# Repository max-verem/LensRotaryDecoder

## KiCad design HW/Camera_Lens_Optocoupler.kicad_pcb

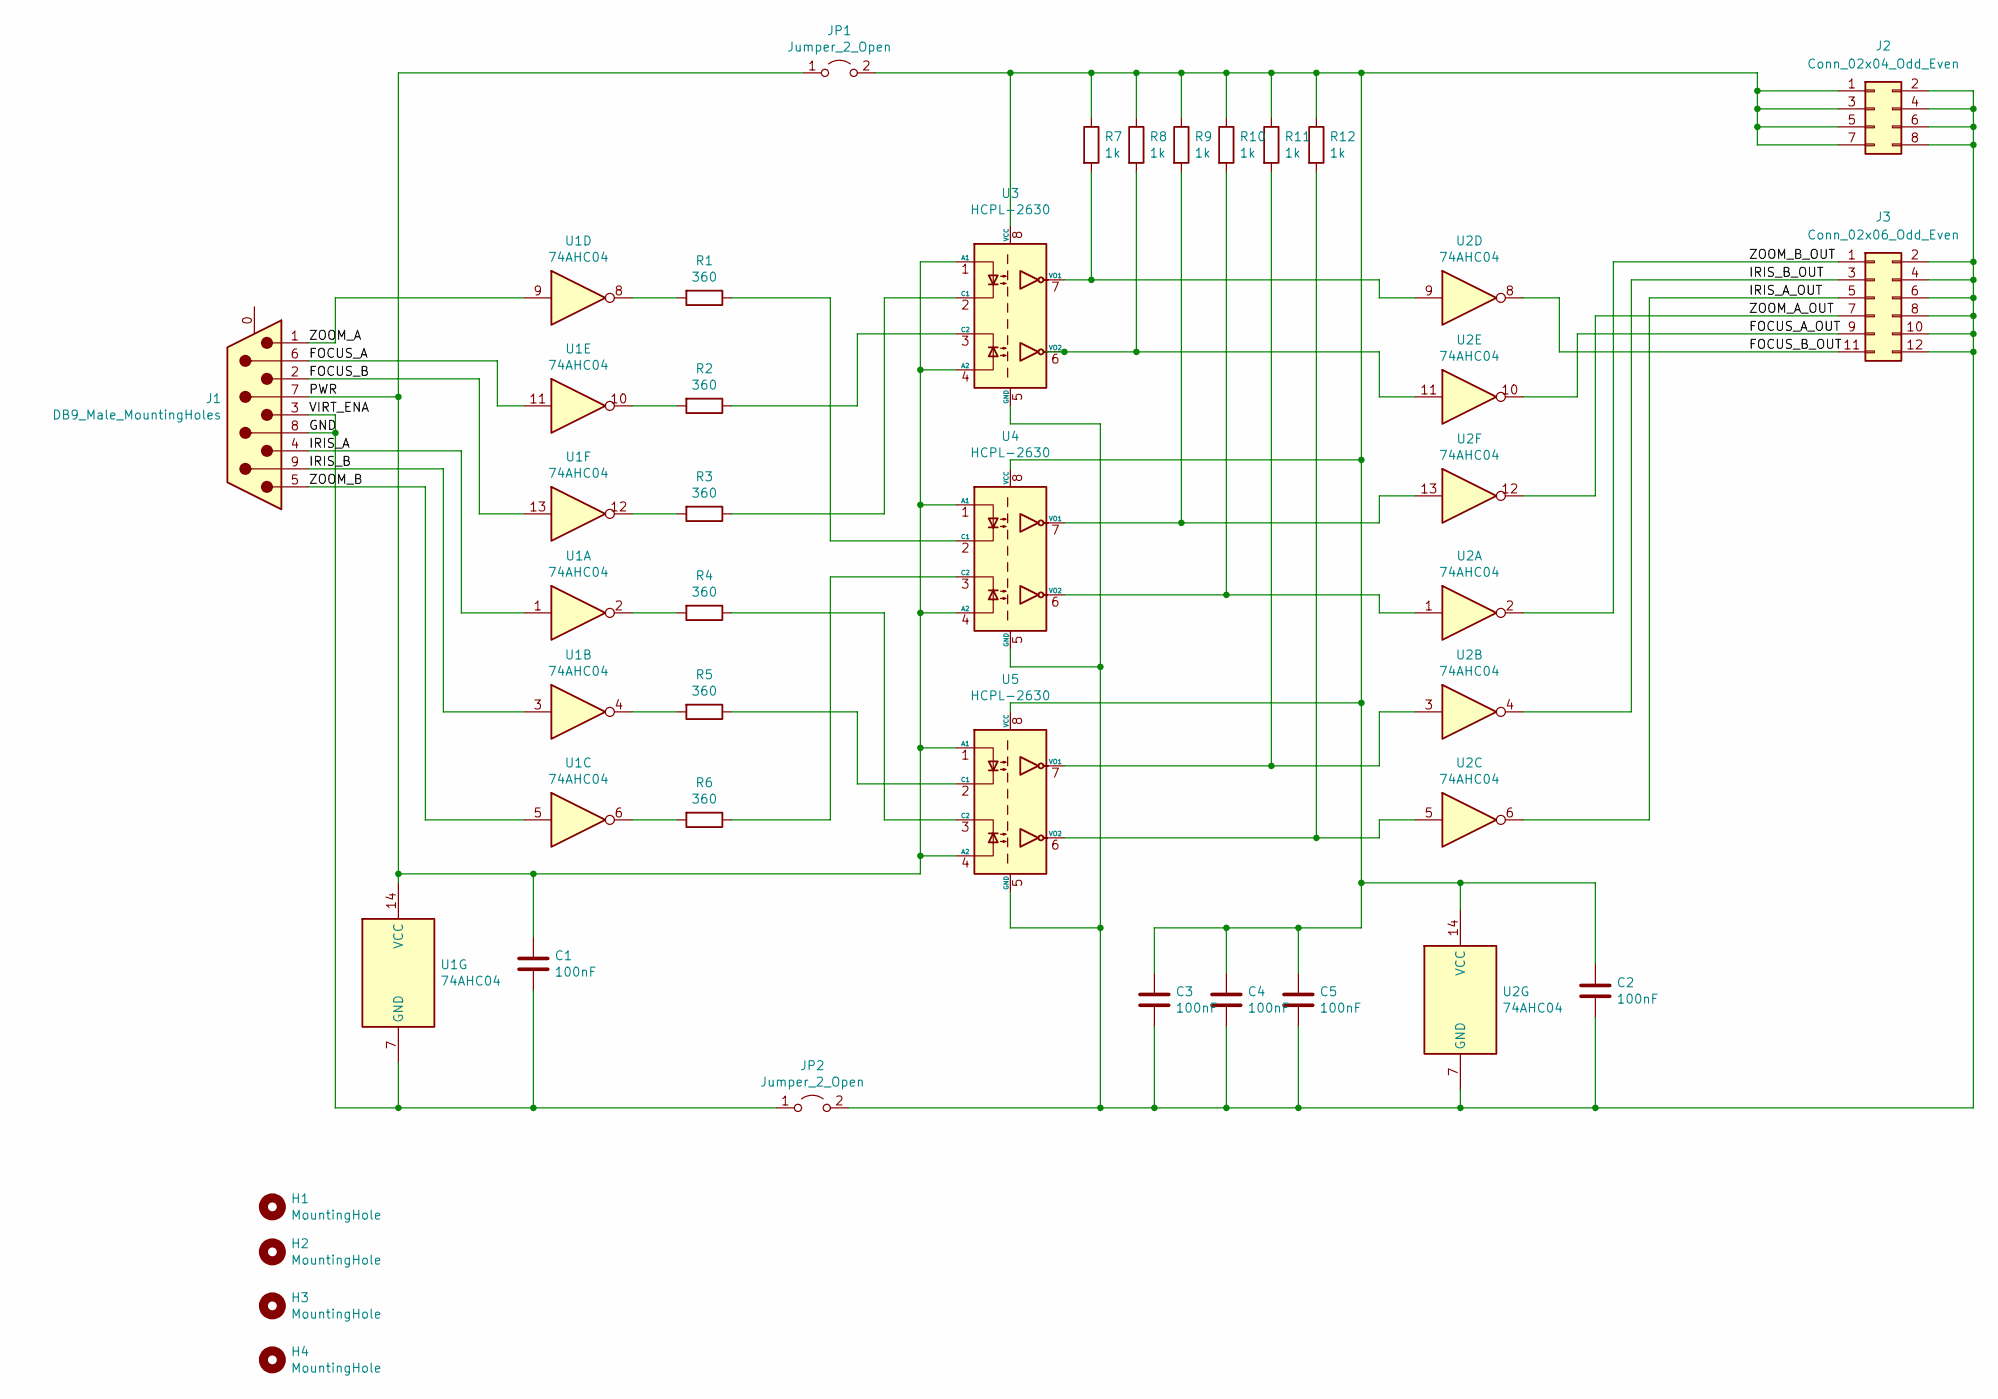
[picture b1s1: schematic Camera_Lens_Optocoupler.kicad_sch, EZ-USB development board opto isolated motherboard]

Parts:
C1, C2, C3, C4, C5: 100nF; C_Rect_L7.0mm_W2.0mm_P5.00mm
H1, H2, H3, H4: MountingHole; MountingHole_3.2mm_M3
J1: DB9_Male_MountingHoles; DSUB-9_Male_Horizontal_P2.77x2.84mm_EdgePinOffset9.90mm_Hou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
J2: Conn_02x04_Odd_Even; PinHeader_2x04_P2.54mm_Horizontal
J3: Conn_02x06_Odd_Even; PinSocket_2x06_P2.54mm_Horizontal
JP1, JP2: Jumper_2_Open; PinHeader_1x02_P2.54mm_Vertical
R1, R2, R3, R4, R5, R6: 360; R_Axial_DIN0309_L9.0mm_D3.2mm_P12.70mm_Horizontal
R7, R8, R9, R10, R11, R12: 1k; R_Axial_DIN0309_L9.0mm_D3.2mm_P12.70mm_Horizontal
U1, U2: 74AHC04; DIP-14_W7.62mm
U3, U4, U5: HCPL-2630; DIP-8_W7.62mm

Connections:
/FOCUS_A: J1.6, U1.11
/FOCUS_A_OUT: J3.9, U2.10
/FOCUS_B: J1.2, U1.13
/FOCUS_B_OUT: J3.11, U2.8
/GND: C1.2, J1.3, J1.8, JP2.1 (A), U1.7 (GND)
/IRIS_A: J1.4, U1.1
/IRIS_A_OUT: J3.5, U2.6
/IRIS_B: J1.9, U1.3
/IRIS_B_OUT: J3.3, U2.4
/PWR: C1.1, J1.7, JP1.1 (A), U1.14 (VCC), U3.1 (A1), U3.4 (A2), U4.1 (A1), U4.4 (A2), U5.1 (A1), U5.4 (A2)
/ZOOM_A: J1.1, U1.9
/ZOOM_A_OUT: J3.7, U2.12
/ZOOM_B: J1.5, U1.5
/ZOOM_B_OUT: J3.1, U2.2
unnamed: C2.1, C3.1, C4.1, C5.1, J2.1, J2.3, J2.5, J2.7, JP1.2 (B), R7.1, R8.1, R9.1, R10.1, R11.1, R12.1, U2.14 (VCC), U3.8 (VCC), U4.8 (VCC), U5.8 (VCC)
unnamed: C2.2, C3.2, C4.2, C5.2, J2.2, J2.4, J2.6, J2.8, J3.2, J3.4, J3.6, J3.8, J3.10, J3.12, JP2.2 (B), U2.7 (GND), U3.5 (GND), U4.5 (GND), U5.5 (GND)
unnamed: R1.1, U4.2 (C1)
unnamed: R1.2, U1.8
unnamed: R2.1, U3.3 (C2)
unnamed: R2.2, U1.10
unnamed: R3.1, U3.2 (C1)
unnamed: R3.2, U1.12
unnamed: R4.1, U5.3 (C2)
unnamed: R4.2, U1.2
unnamed: R5.1, U5.2 (C1)
unnamed: R5.2, U1.4
unnamed: R6.1, U4.3 (C2)
unnamed: R6.2, U1.6
unnamed: R7.2, U2.9, U3.7 (VO1)
unnamed: R8.2, U2.11, U3.6 (VO2)
unnamed: R9.2, U2.13, U4.7 (VO1)
unnamed: R10.2, U2.1, U4.6 (VO2)
unnamed: R11.2, U2.3, U5.7 (VO1)
unnamed: R12.2, U2.5, U5.6 (VO2)

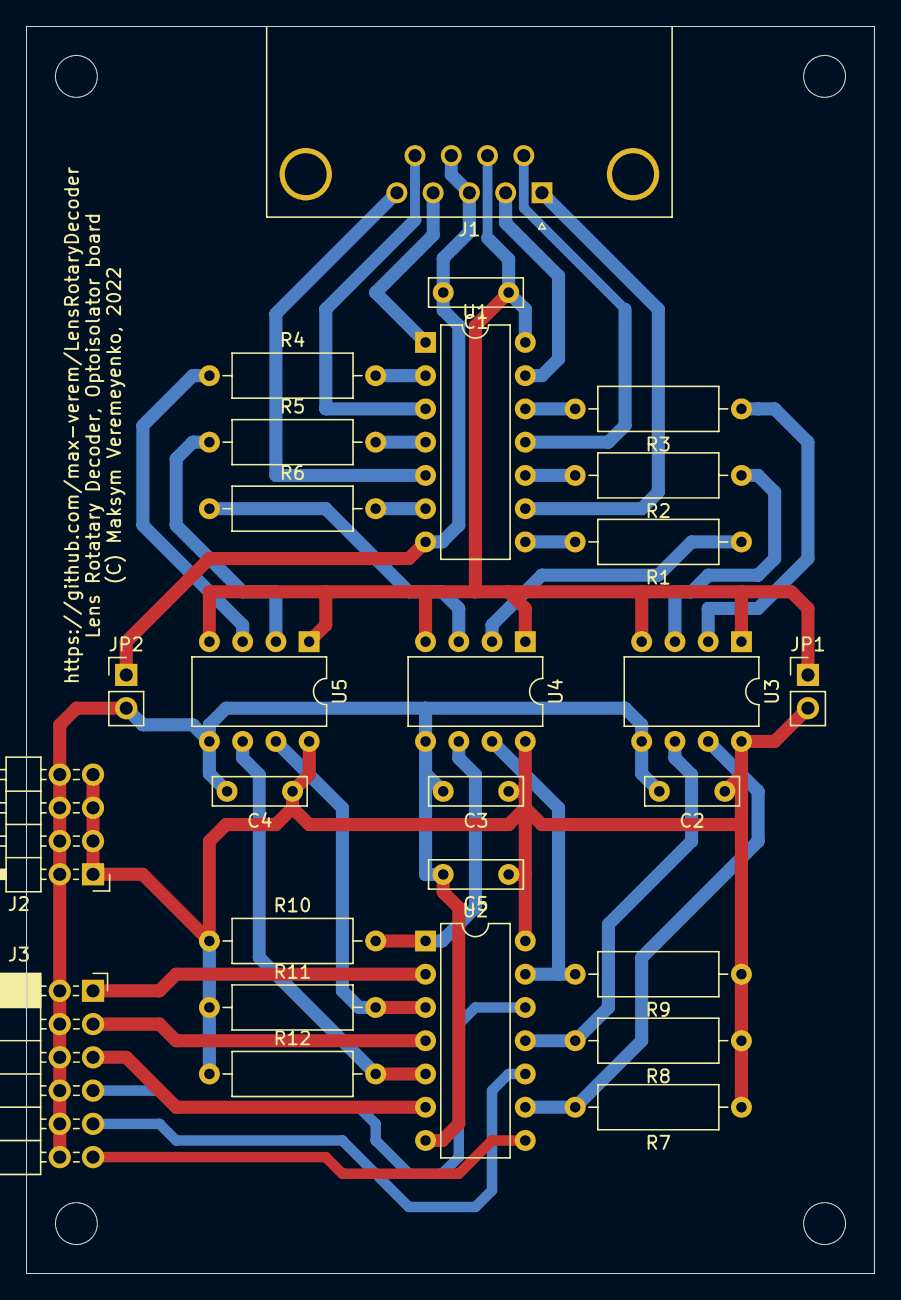
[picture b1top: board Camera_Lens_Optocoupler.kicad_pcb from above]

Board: 2 copper layers, 64.8 x 95.2 mm, 31 parts (0 on the bottom side), 34 nets.

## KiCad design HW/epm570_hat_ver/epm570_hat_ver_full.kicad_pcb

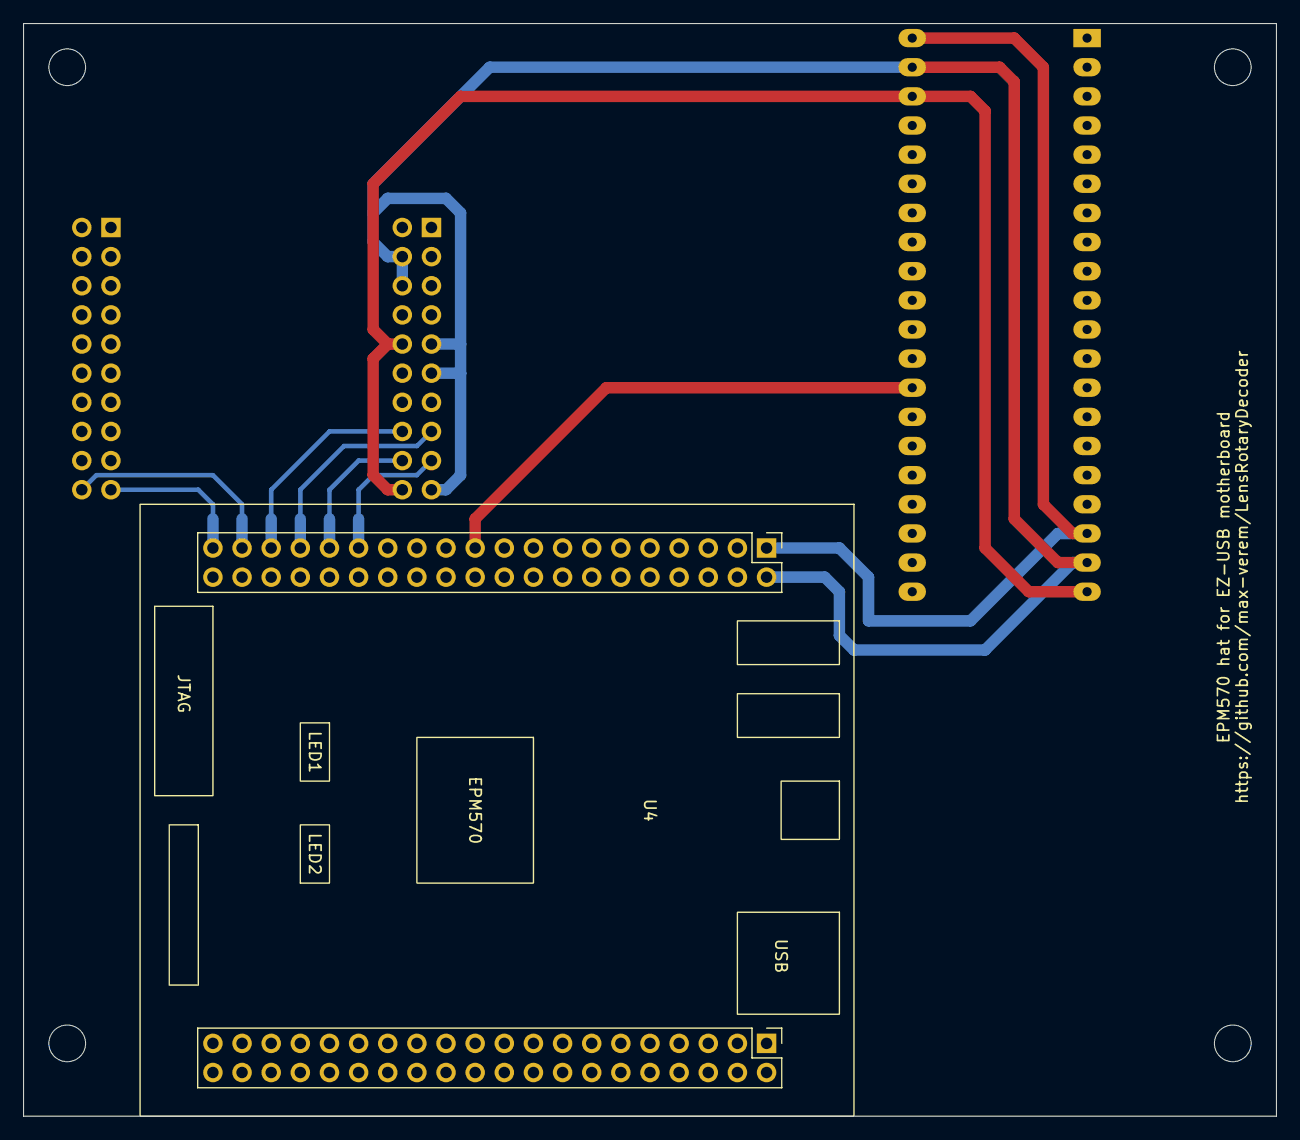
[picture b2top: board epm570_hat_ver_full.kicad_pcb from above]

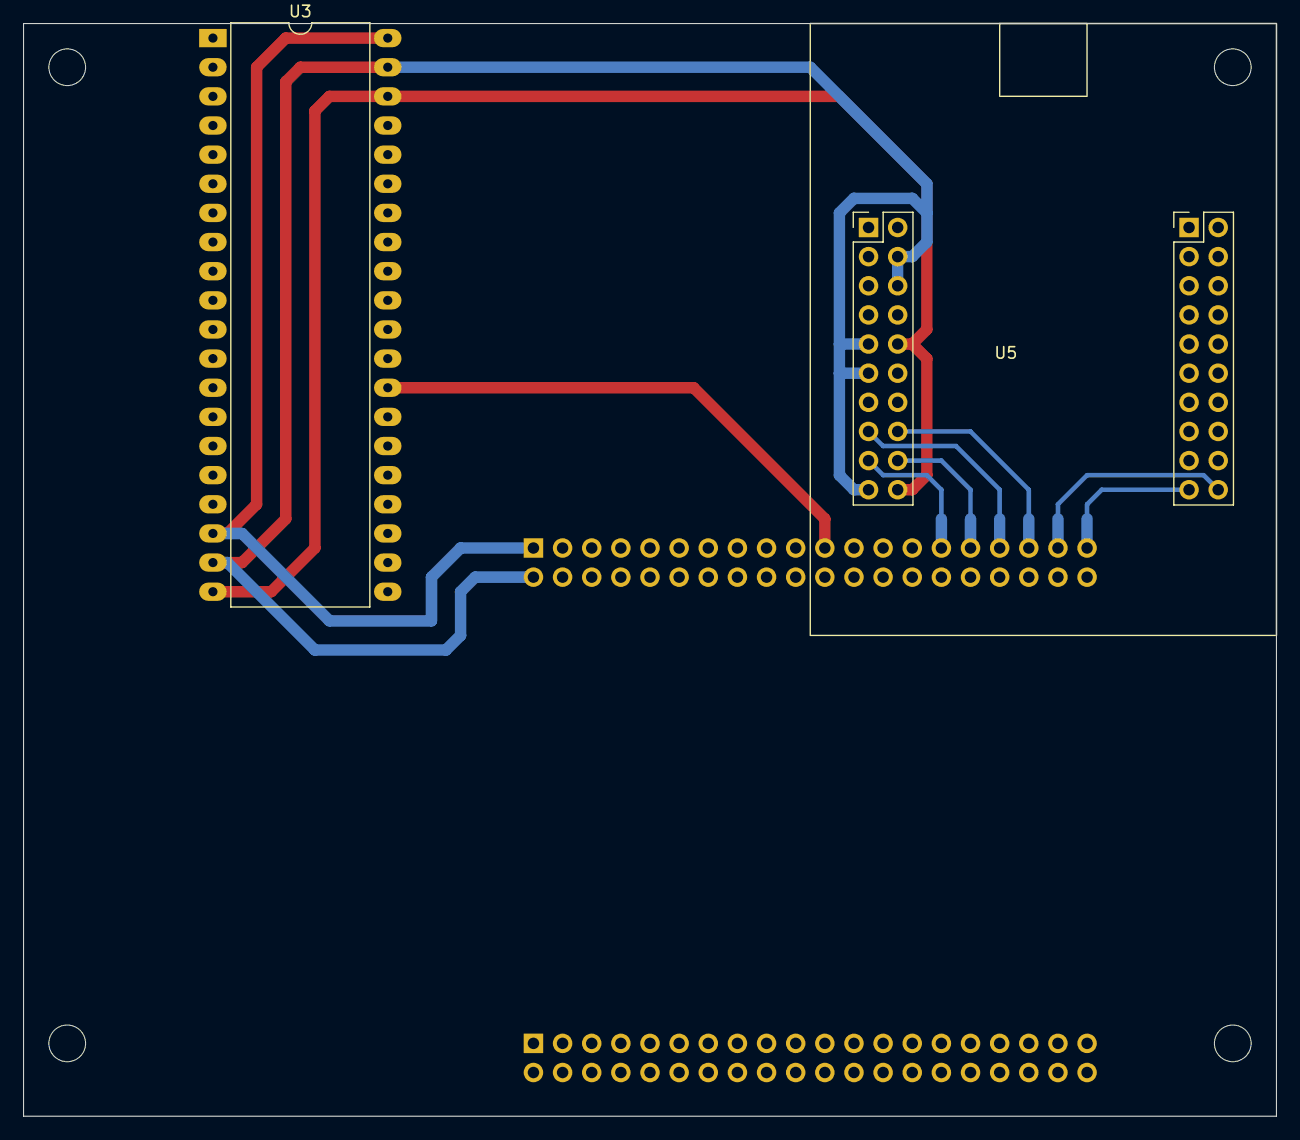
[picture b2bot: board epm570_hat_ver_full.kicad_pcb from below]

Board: 2 copper layers, 109.2 x 95.2 mm, 7 parts (2 on the bottom side), 10 nets.

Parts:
H1, H2, H3, H4: MountingHole; MountingHole_3.2mm_M3
U3: STM32F4x1Cx_v2.0+; DIP-40_W15.24mm_LongPads
U4: EPM570_DEV_BOARD
U5: CY7C68013A_EZ-USB_FX2LP

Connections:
/GND: U3.19 (G), U3.39 (G), U4.2 (GND), U5.4 (GND), U5.6 (GND), U5.9 (GND), U5.11 (GND), U5.19 (GND)
/OUT_FOCUS_A: U4.29 (PORT20), U5.17 (PB2)
/OUT_FOCUS_B: U4.31 (PORT26), U5.18 (PB3)
/OUT_IRIS_A: U4.37 (PORT34), U5.40 (PB4)
/OUT_IRIS_B: U4.39 (PORT36), U5.39 (PB5)
/OUT_ZOOM_A: U4.33 (PORT28), U5.15 (PB0)
/OUT_ZOOM_B: U4.35 (PORT30), U5.16 (PB1)
/PWIN: U3.18 (5V), U3.40 (5V), U4.1 (PWIN)
/TX2: U3.28 (PA2), U4.21 (PORT8)
/VCC: U3.20 (3V3), U3.38 (3V3), U5.10 (VCC), U5.20 (VCC)
